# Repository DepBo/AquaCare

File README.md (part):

# AquaCare

AquaCare là hệ thống theo dõi và quản lý nuôi trồng thủy sản, gồm ứng dụng web, ứng dụng di động và backend kết nối dữ liệu cảm biến với thiết bị trong ao/bể.

Trong quá trình nuôi, chất lượng nước và trạng thái thiết bị có thể thay đổi nhanh, trong khi việc kiểm tra thủ công thường tốn thời gian và khó theo dõi liên tục. AquaCare tập trung đưa dữ liệu từ thiết bị IoT về một nơi để người nuôi theo dõi, nhận cảnh báo và chủ động điều khiển một số thiết bị từ xa. Hệ thống đồng thời cung cấp các màn hình quản lý cho khách hàng, nhân viên và quản trị viên.

## Giới thiệu chức năng

### Theo dõi môi trường nuôi

Thiết bị gửi dữ liệu cảm biến về hệ thống thông qua MQTT. Backend tiếp nhận dữ liệu, xử lý và lưu vào Supabase để các ứng dụng truy vấn. Các chỉ số được sử dụng trong luồng theo dõi bao gồm nhiệt độ nước, độ pH, TDS và trạng thái mực nước. Dashboard giúp người dùng quan sát tình trạng hiện tại; phần lịch sử hỗ trợ xem lại biến động theo thời gian.

Ngưỡng đánh giá có thể được cấu hình theo loài nuôi. Dữ liệu được phân loại thành trạng thái bình thường, cần chú ý hoặc nguy hiểm để người vận hành nhận biết nhanh khi môi trường vượt khỏi khoảng phù hợp.

### Cảnh báo và thông báo

Khi chỉ số vượt ngưỡng hoặc phát hiện điều kiện bất thường, backend tạo cảnh báo gắn với bể và thiết bị liên quan. Hệ thống hỗ trợ gửi email và thông báo đẩy Firebase Cloud Messaging khi thông tin dịch vụ đã được cấu hình. Cơ chế xử lý cảnh báo có lọc và gộp trạng thái nhằm hạn chế gửi lặp liên tục cho cùng một tình trạng.

### Điều khiển thiết bị

Người dùng có thể gửi lệnh điều khiển relay từ giao diện. Backend xác định thiết bị theo bể nuôi, phát lệnh qua MQTT và cập nhật trạng thái vào cơ sở dữ liệu. Endpoint lệnh thô cho phép chuyển một chuỗi lệnh tới thiết bị theo giao thức phần cứng đã triển khai. Tác vụ hẹn giờ chạy trong backend hỗ trợ các luồng điều khiển có lịch.

### Tài khoản và phân quyền

Hệ thống có luồng đăng ký, đăng nhập và khôi phục mật khẩu. Khu vực sau đăng nhập được phân theo vai trò: khách hàng sử dụng dashboard nuôi trồng; nhân viên truy cập màn hình nghiệp vụ; quản trị viên quản lý cấu hình và dữ liệu hệ thống. Các trang bảo vệ kiểm tra phiên Supabase và vai trò người dùng trước khi hiển thị.

### Quản lý vận hành và dịch vụ

Giao diện quản trị có các khu vực quản lý loài cá, thiết bị, nhân viên, đơn hàng và gói dịch vụ. Dữ liệu thiết bị có thể được theo dõi theo phiên bản và trạng thái sử dụng/kho. Quản trị viên cũng có thể cấu hình các khoảng ngưỡng nhiệt độ, pH và TDS theo loài, giúp hệ thống đánh giá dữ liệu sát với đối tượng nuôi.

Ứng dụng web còn có các trang giới thiệu sản phẩm và gói đăng ký, giỏ hàng, dashboard khách hàng và các trang nhân viên. Ứng dụng Flutter cung cấp trải nghiệm di động với các màn hình tổng quan, cảnh báo, điều khiển và quản trị.

### Kiến trúc tổng quan

```text
Cảm biến / thiết bị IoT
        │ MQTT telemetry và lệnh điều khiển
        ▼
Backend Node.js + Express ───── Firebase: thông báo đẩy
        │                       Email: cảnh báo
        ▼
     Supabase
        ▲
        ├── AquaCare Web (React + TypeScript)
        └── AquaCare App (Flutter)
```

Backend nhận telemetry và xử lý cảnh báo, đồng thời cung cấp API cho đăng nhập, dashboard quản trị và điều khiển thiết bị. Web và ứng dụng di động đọc dữ liệu nghiệp vụ qua Supabase, sử dụng API backend cho các thao tác tương ứng. Supabase đảm nhiệm lưu trữ và xác thực dữ liệu; MQTT là kênh liên lạc với thiết bị.

## Chức năng chính

- Theo dõi dữ liệu chất lượng nước như pH, nhiệt độ, TDS và mực nước.
- Hiển thị lịch sử dữ liệu, trạng thái thiết bị và cảnh báo theo ngưỡng của từng loài.
- Điều khiển relay và gửi lệnh tới phần cứng qua MQTT.
- Quản lý tài khoản, bể nuôi, thiết bị, nhân viên, sản phẩm và gói dịch vụ.
- Gửi cảnh báo email và thông báo đẩy khi được cấu hình.
- Cung cấp giao diện quản trị trên web và ứng dụng di động.

## AquaCare giải quyết vấn đề gì?

Quản lý ao nuôi đòi hỏi người vận hành theo dõi chất lượng nước thường xuyên, nhận biết sớm các dấu hiệu bất thường và phản ứng kịp thời. Khi số lượng bể tăng lên, việc ghi chép thủ công khiến dữ liệu khó tổng hợp, khó đối chiếu và có thể bỏ lỡ những thay đổi quan trọng giữa các lần kiểm tra.

AquaCare kết hợp thiết bị cảm biến, phần mềm và lưu trữ dữ liệu để hỗ trợ các công việc đó trên cùng một hệ thống. Người dùng có thể xem thông tin từ nhiều bể, tra cứu lại lịch sử, nhận cảnh báo khi chỉ số lệch khỏi ngưỡng, và gửi lệnh đến các thiết bị được kết nối. Ngoài theo dõi kỹ thuật, hệ thống còn có các chức năng quản lý người dùng, nhân viên, thiết bị, đơn hàng và gói dịch vụ.

> AquaCare là công cụ hỗ trợ quan sát và vận hành. Chất lượng kết quả phụ thuộc vào việc hiệu chuẩn cảm biến, kết nối mạng, cấu hình ngưỡng và cấu hình dịch vụ ngoài hệ thống.

## Các nhóm người dùng

### Khách hàng và người nuôi

Khách hàng sử dụng dashboard để xem bể nuôi thuộc tài khoản của mình, theo dõi các chỉ số môi trường và lịch sử, xem cảnh báo, cũng như sử dụng các thao tác điều khiển được cấp quyền. Giao diện web và ứng dụng di động hướng đến việc giúp người nuôi nắm nhanh tình trạng tổng thể rồi mở thông tin chi tiết khi cần.

Khu vực khách hàng trên web còn có các nội dung giới thiệu sản phẩm, gói dịch vụ, giỏ hàng và thông tin liên hệ. Việc truy cập các màn hình được bảo vệ dựa trên phiên xác thực và vai trò tài khoản.

### Nhân viên

Khu vực nhân viên phục vụ các tác vụ vận hành được phân công. Backend dashboard tổng hợp những thông tin như đơn hàng chờ xử lý, công việc đóng gói, đơn đang giao, thiết bị đã được gán và số lượng nhân viên. Màn hình quản trị còn tổ chức vai trò nhân viên theo nhóm công việc như kho, giao hàng, hỗ trợ và bảo trì.

### Quản trị viên

Quản trị viên quản lý cấu hình và dữ liệu vận hành của hệ thống. Các phân hệ hiện diện trong giao diện gồm tổng quan, loài nuôi, thiết bị, nhân viên, đơn hàng và gói cước. Tùy dữ liệu và quyền đã thiết lập, quản trị viên có thể quản lý thông tin loài, ngưỡng môi trường, phân bổ thiết bị, tài khoản nhân viên, trạng thái đơn hàng và đặc tính các gói dịch vụ.

## Mô tả chức năng chi tiết

### 1. Dashboard và quản lý bể nuôi

Dashboard tập trung thông tin theo bể nuôi để người vận hành không phải truy cập nhiều nguồn dữ liệu riêng lẻ. Tùy cấu hình dữ liệu, dashboard hiển thị thông số mới nhất, trạng thái chất lượng nước, cảnh báo và hoạt động điều khiển. Người dùng có thể chọn bể cần xem và đi sâu vào biểu đồ hoặc lịch sử cảm biến.

Các thành phần giao diện hỗ trợ tổng quan bể và phân tích lịch sử. Ứng dụng Flutter có màn hình tổng quan, màn hình chi tiết cảm biến và các tiện ích biểu đồ cảnh báo. Giao diện web có dashboard khách hàng và bảng điều khiển thiết bị.

### 2. Giám sát cảm biến và lịch sử

Backend nhận telemetry theo topic MQTT của thiết bị, đối chiếu thiết bị với bể trong cơ sở dữ liệu, sau đó lưu các giá trị hợp lệ vào bảng lịch sử. Các luồng dữ liệu hiện có đề cập đến pH, nhiệt độ, TDS và tình trạng mực nước. Người dùng có thể xem lại dữ liệu theo thời gian nhằm nhận biết xu hướng thay đổi, thay vì chỉ nhìn vào một số đo tại thời điểm hiện tại.

Lịch sử cũng giúp việc xem xét cảnh báo có thêm bối cảnh: người vận hành có thể đánh giá chỉ số đã thay đổi ra sao, bất thường mới xuất hiện hay đã kéo dài, và cần kiểm tra thiết bị hoặc nguồn nước hay không. Độ chính xác của kết luận phụ thuộc vào cảm biến và tần suất thiết bị gửi dữ liệu.

### 3. Đánh giá ngưỡng theo loài

Mỗi loài thủy sản có điều kiện môi trường phù hợp khác nhau. AquaCare tổ chức cấu hình ngưỡng theo loài để backend và giao diện có thể so sánh dữ liệu cảm biến với khoảng đánh giá tương ứng. Với các chỉ số có ngưỡng tốt và ngưỡng cảnh báo, dữ liệu được phân loại thành `Good`, `Warn` hoặc `Danger`.

Quản trị viên có thể quản lý loài và các khoảng giá trị môi trường được hệ thống sử dụng. Nên xác minh ngưỡng với yêu cầu thực tế của đối tượng nuôi trước khi đưa vào vận hành; cài đặt ứng dụng không thay thế tư vấn chuyên môn hoặc hiệu chuẩn thiết bị.

### 4. Cảnh báo môi trường

Khi chỉ số nằm ngoài khoảng được cấu hình hoặc trạng thái mực nước không bình thường, backend có thể ghi nhận sự kiện vào lịch sử cảnh báo. Cảnh báo được gắn với bể, thiết bị, loại chỉ số, giá trị thực tế và nội dung mô tả để tiện tra cứu.

Luồng cảnh báo có thể kiểm tra cấu hình nhận thông báo của bể, thông tin tài khoản và thời điểm cảnh báo gần nhất. Bộ lọc cooldown/gộp trạng thái giúp hạn chế việc phát đi nhiều thông báo lặp trong một khoảng ngắn. Người vận hành vẫn có thể mở màn hình cảnh báo để xem sự kiện đã lưu.

### 5. Gửi email và thông báo đẩy

Backend hỗ trợ email cảnh báo. Khi cấu hình `BREVO_API_KEY`, email được gửi qua API HTTPS của Brevo; nếu không có khóa này, backend có thể dùng Gmail SMTP với `EMAIL_USER` và `EMAIL_PASS` khi môi trường cho phép. Chi tiết cấu hình triển khai email được ghi trong `AquaCare_Backend/ALERT_EMAIL.md`.

Thông báo đẩy được tích hợp qua Firebase Cloud Messaging. Ứng dụng web có luồng xin quyền trình duyệt và lấy token; ứng dụng Flutter khởi tạo Firebase Messaging và đồng bộ token sau khi đăng nhập. Backend cần thông tin Firebase Admin hợp lệ để gửi thông báo. Người dùng cũng cần cấp quyền thông báo trên trình duyệt hoặc thiết bị.

### 6. Điều khiển relay và lệnh MQTT

Từ bảng điều khiển, người dùng có thể gửi yêu cầu bật/tắt relay. Backend nhận mã bể, chân relay, trạng thái mong muốn và trường trạng thái cần cập nhật. Sau đó backend tra thiết bị theo mã bể, lấy địa chỉ MAC, gửi thông điệp MQTT tới topic lệnh của thiết bị và lưu trạng thái relay vào Supabase.

Endpoint gửi lệnh thô nhận mã bể cùng chuỗi lệnh, sau đó chuyển lệnh đến topic MQTT tương ứng với địa chỉ MAC. Lệnh chính xác cần phù hợp giao thức firmware của thiết bị. Việc gửi lệnh chỉ được xem là thành công hoàn toàn khi thiết bị nhận và thực hiện lệnh; phản hồi HTTP của backend chủ yếu xác nhận quá trình gửi/xử lý ở phía server.

### 7. Lịch điều khiển và mô phỏng phần cứng

Backend có worker xử lý tác vụ hẹn giờ và lịch điều khiển thiết bị. Web có tiện ích xử lý thời gian lịch thiết bị, còn backend có `timer_worker.js` để kiểm tra và phát lệnh theo lịch đã lưu. `hardware_simulator.js` hỗ trợ mô phỏng gửi telemetry trong quá trình phát triển hoặc trình diễn khi chưa có thiết bị thật; cần cấu hình Supabase trước khi chạy.

### 8. Đăng nhập và quản lý phiên

Web có màn hình đăng nhập, đăng ký, quên mật khẩu và đặt lại mật khẩu. Backend cung cấp API đăng ký/đăng nhập, trong khi Supabase được dùng cho xác thực và dữ liệu hồ sơ. Các trang dashboard, nhân viên và quản trị viên kiểm tra vai trò trước khi cho truy cập. Nếu phiên không hợp lệ hoặc vai trò không khớp với khu vực được yêu cầu, ứng dụng chuyển người dùng về trang phù hợp.

Ứng dụng di động có màn hình khởi động, hướng dẫn ban đầu, đăng nhập và đăng ký. Ứng dụng có thể ghi nhớ lựa chọn đăng nhập, khôi phục phiên khi khởi chạy và điều hướng theo vai trò đã xác thực.

### 9. Quản trị thiết bị

Phân hệ thiết bị tập trung thông tin gắn với bể, địa chỉ MAC, phiên bản phần cứng và trạng thái sử dụng. Màn hình quản trị cung cấp bộ lọc theo phiên bản thiết bị (V1–V4) và trạng thái như đang dùng, đã được mua hoặc còn trong kho. Việc gán đúng thiết bị với đúng bể là điều kiện để backend định tuyến lệnh MQTT và gắn telemetry với dữ liệu nuôi.

### 10. Quản lý loài và điều kiện nuôi

Danh mục loài giúp hệ thống lưu thông tin đối tượng nuôi và các ngưỡng môi trường áp dụng. Dữ liệu này được dùng ở cả khâu đánh giá cảm biến lẫn giao diện hiển thị trạng thái. Khi tạo hoặc cập nhật ngưỡng, cần đảm bảo giá trị nhỏ nhất không lớn hơn giá trị lớn nhất và các khoảng tốt/cảnh báo được thiết lập nhất quán.

### 11. Quản lý nhân viên và công việc

Quản trị viên có thể tổ chức nhân viên theo vai trò nghiệp vụ. Dashboard backend hiện tổng hợp một số chỉ số vận hành, bao gồm số nhân viên, đơn hàng chờ xử lý, công việc đóng gói đang thực hiện và đơn đang giao. Những dữ liệu này giúp theo dõi công việc nội bộ song song với tình trạng kỹ thuật của thiết bị.

### 12. Sản phẩm, đơn hàng và gói dịch vụ

Web có trang sản phẩm, gói đăng ký và giỏ hàng. Schema cơ sở dữ liệu có các bảng liên quan đến sản phẩm, đơn hàng, chi tiết đơn, mục giỏ hàng, gói đăng ký và đăng ký gói của người dùng. Phần quản trị đơn hàng hỗ trợ theo dõi các trạng thái như chờ duyệt, đã duyệt, đang giao và đã giao.

### 13. Giao diện web và ứng dụng di động

Web được xây dựng bằng React, TypeScript và Vite. Ứng dụng Flutter chứa các màn hình khách hàng, cảnh báo, điều khiển, nhân viên và quản trị, sử dụng chung Supabase làm nguồn dữ liệu nghiệp vụ. Tùy vai trò và nền tảng, một số tính năng hoặc cấu hình thông báo có thể khác nhau.

### 14. Cấu hình giao diện khách hàng

Ứng dụng di động lưu tùy chọn giao diện khách hàng và hỗ trợ tùy chỉnh chế độ sáng/tối. Giao diện dashboard và các biểu đồ giúp trình bày thông tin môi trường theo dạng trực quan hơn để người vận hành dễ nhận biết điểm cần chú ý.

## Cấu trúc dự án

```text
AquaCare/
├── AquaCare_Backend/   # API Express, MQTT, xử lý cảnh báo và tác vụ hẹn giờ
├── AquaCare_Web/       # Giao diện React + TypeScript, chạy bằng Vite
├── AquaCare_App/       # Ứng dụng Flutter cho Android, iOS, Windows và các nền tảng Flutter hỗ trợ
├── migrations/         # Các tệp migration cơ sở dữ liệu
├── schema.sql          # Schema cơ sở dữ liệu
├── database.txt        # Tài liệu/thông tin cơ sở dữ liệu
└── README.md
```

## Yêu cầu

- Node.js và npm.
- Flutter SDK tương thích với phiên bản Dart trong `AquaCare_App/pubspec.yaml`.
- Tài khoản/dự án Supabase đã được thiết lập schema.
- Tài khoản Firebase nếu cần gửi thông báo đẩy; thông tin broker MQTT nếu cần kết nối phần cứng.

## Chạy backend

```bash
cd AquaCare_Backend
npm install
node server.js
```

Backend mặc định chạy tại `http://localhost:5000`. Kiểm tra trạng thái bằng `GET /api/health`.

Tạo `AquaCare_Backend/.env` với các giá trị phù hợp:

```dotenv
PORT=5000
SUPABASE_URL=https://<project-ref>.supabase.co
SUPABASE_SERVICE_ROLE_KEY=<supabase-service-role-key>

# Email cảnh báo: dùng SMTP Gmail khi chạy local
EMAIL_USER=<email>
EMAIL_PASS=<app-password>

# Tùy chọn trên môi trường triển khai: gửi email qua Brevo HTTPS
BREVO_API_KEY=<brevo-api-key>
ALERT_EMAIL_FROM=<verified-sender-email>

# Firebase Admin: JSON service account được tuần tự hóa thành một dòng
FIREBASE_SERVICE_ACCOUNT=<service-account-json>
```

Nếu không đặt `FIREBASE_SERVICE_ACCOUNT`, backend tìm tệp `config/firebase-service-account.json`. Không commit tệp khóa hoặc biến môi trường chứa bí mật. Thông tin kết nối HiveMQ hiện được khai báo trong `AquaCare_Backend/server.js`; chuyển các thông tin đó sang biến môi trường trước khi sử dụng cấu hình broker riêng hoặc công khai mã nguồn.

## Chạy ứng dụng web

```bash
cd AquaCare_Web
npm install
npm run dev
```

Vite in địa chỉ truy cập local ra terminal (thông thường là `http://localhost:5173`). Các lệnh có sẵn:

```bash
npm run build
npm run preview
```

Có thể tạo `AquaCare_Web/.env.local` để cấu hình dịch vụ:

```dotenv
VITE_API_URL=http://localhost:5000
VITE_SUPABASE_URL=https://<project-ref>.supabase.co
VITE_SUPABASE_ANON_KEY=<supabase-anon-key>
```

Web có URL mặc định cho backend triển khai. Khi phát triển local, cần đặt `VITE_API_URL` để các API đăng nhập, điều khiển thiết bị và dashboard trỏ tới backend local. Các biến `VITE_*` được đưa vào mã phía trình duyệt; chỉ dùng khóa Supabase anon/public key, tuyệt đối không đưa service role key vào web.

## Chạy ứng dụng Flutter

Tạo `AquaCare_App/.env`:

```dotenv
SUPABASE_URL=https://<project-ref>.supabase.co
SUPABASE_ANON_KEY=<supabase-anon-key>
```

Sau đó chạy:

```bash
cd AquaCare_App
flutter pub get
flutter run
```

Ứng dụng cũng hỗ trợ URL backend dashboard qua Dart define:

```bash
flutter run --dart-define=ADMIN_DASHBOARD_API_URL=http://localhost:5000
```

## API chính

| Phương thức | Đường dẫn | Mô tả |
|---|---|---|
| `GET` | `/api/health` | Kiểm tra backend hoạt động |
| `POST` | `/api/auth/register` | Đăng ký tài khoản |
| `POST` | `/api/auth/login` | Đăng nhập |
| `GET` | `/api/admin/dashboard` | Dữ liệu dashboard quản trị |
| `POST` | `/api/device/relay` | Điều khiển relay qua MQTT |
| `POST` | `/api/device/command` | Gửi lệnh thô tới thiết bị qua MQTT |

Các API quản trị yêu cầu phiên đăng nhập và quyền admin. Payload chi tiết xem trong mã nguồn tại `AquaCare_Backend/routes/` và phần xử lý endpoint thiết bị trong `AquaCare_Backend/server.js`.

## Cơ sở dữ liệu và kiểm tra

- Dùng `schema.sql` để tham khảo schema ban đầu; các cập nhật sau có thể nằm trong `migrations/`.
- Backend có các bài kiểm tra Node.js trong `AquaCare_Backend/test/`.
- Web có kiểm tra trong `AquaCare_Web/tests/`.
- Ứng dụng Flutter dùng cấu hình và lệnh chuẩn của Flutter; xem `AquaCare_App/README.md`.

## Bảo mật

- Không commit `.env`, khóa Supabase service role, Firebase service account hoặc mật khẩu email.
- Chỉ dùng Supabase anon key trong ứng dụng web/di động và cấu hình Row Level Security phù hợp trong Supabase.
- Các credential MQTT đang có trong mã nguồn backend cần được thay/thu hồi nếu repository từng được chia sẻ công khai.
- Giới hạn CORS và cấu hình endpoint theo các domain triển khai thực tế trước khi đưa hệ thống lên production.

## AquaCare giải quyết vấn đề gì?

Quản lý ao nuôi đòi hỏi người vận hành theo dõi chất lượng nước thường xuyên, nhận biết sớm dấu hiệu bất thường và phản ứng kịp thời. Khi số lượng bể tăng, ghi chép thủ công khiến dữ liệu khó tổng hợp và có thể bỏ lỡ thay đổi giữa các lần kiểm tra. AquaCare kết hợp thiết bị cảm biến, phần mềm và lưu trữ dữ liệu để người dùng xem tình trạng nhiều bể, tra cứu lịch sử, nhận cảnh báo và điều khiển thiết bị từ xa. Hệ thống cũng có các chức năng quản lý nhân viên, thiết bị, đơn hàng và gói dịch vụ.

> AquaCare là công cụ hỗ trợ quan sát và vận hành. Kết quả phụ thuộc vào độ chính xác cảm biến, kết nối mạng, ngưỡng cấu hình và dịch vụ ngoài hệ thống.

## Nhóm người dùng

### Khách hàng và người nuôi

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
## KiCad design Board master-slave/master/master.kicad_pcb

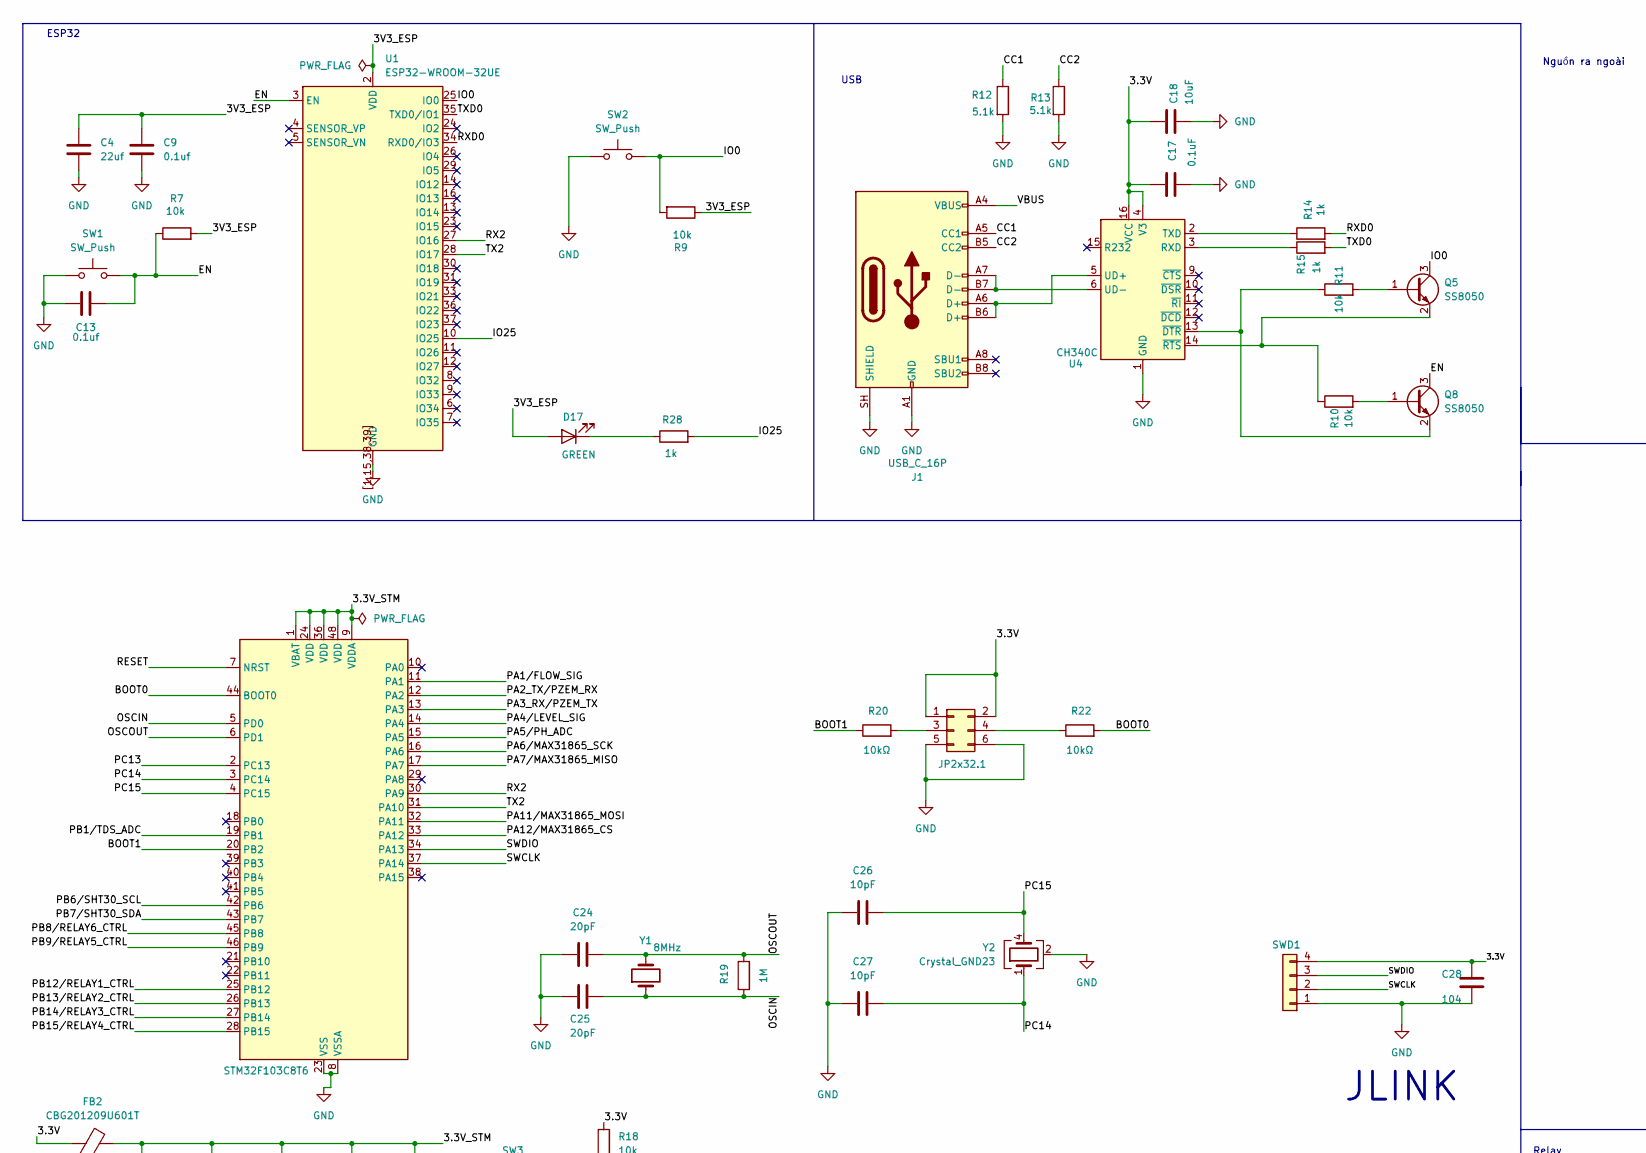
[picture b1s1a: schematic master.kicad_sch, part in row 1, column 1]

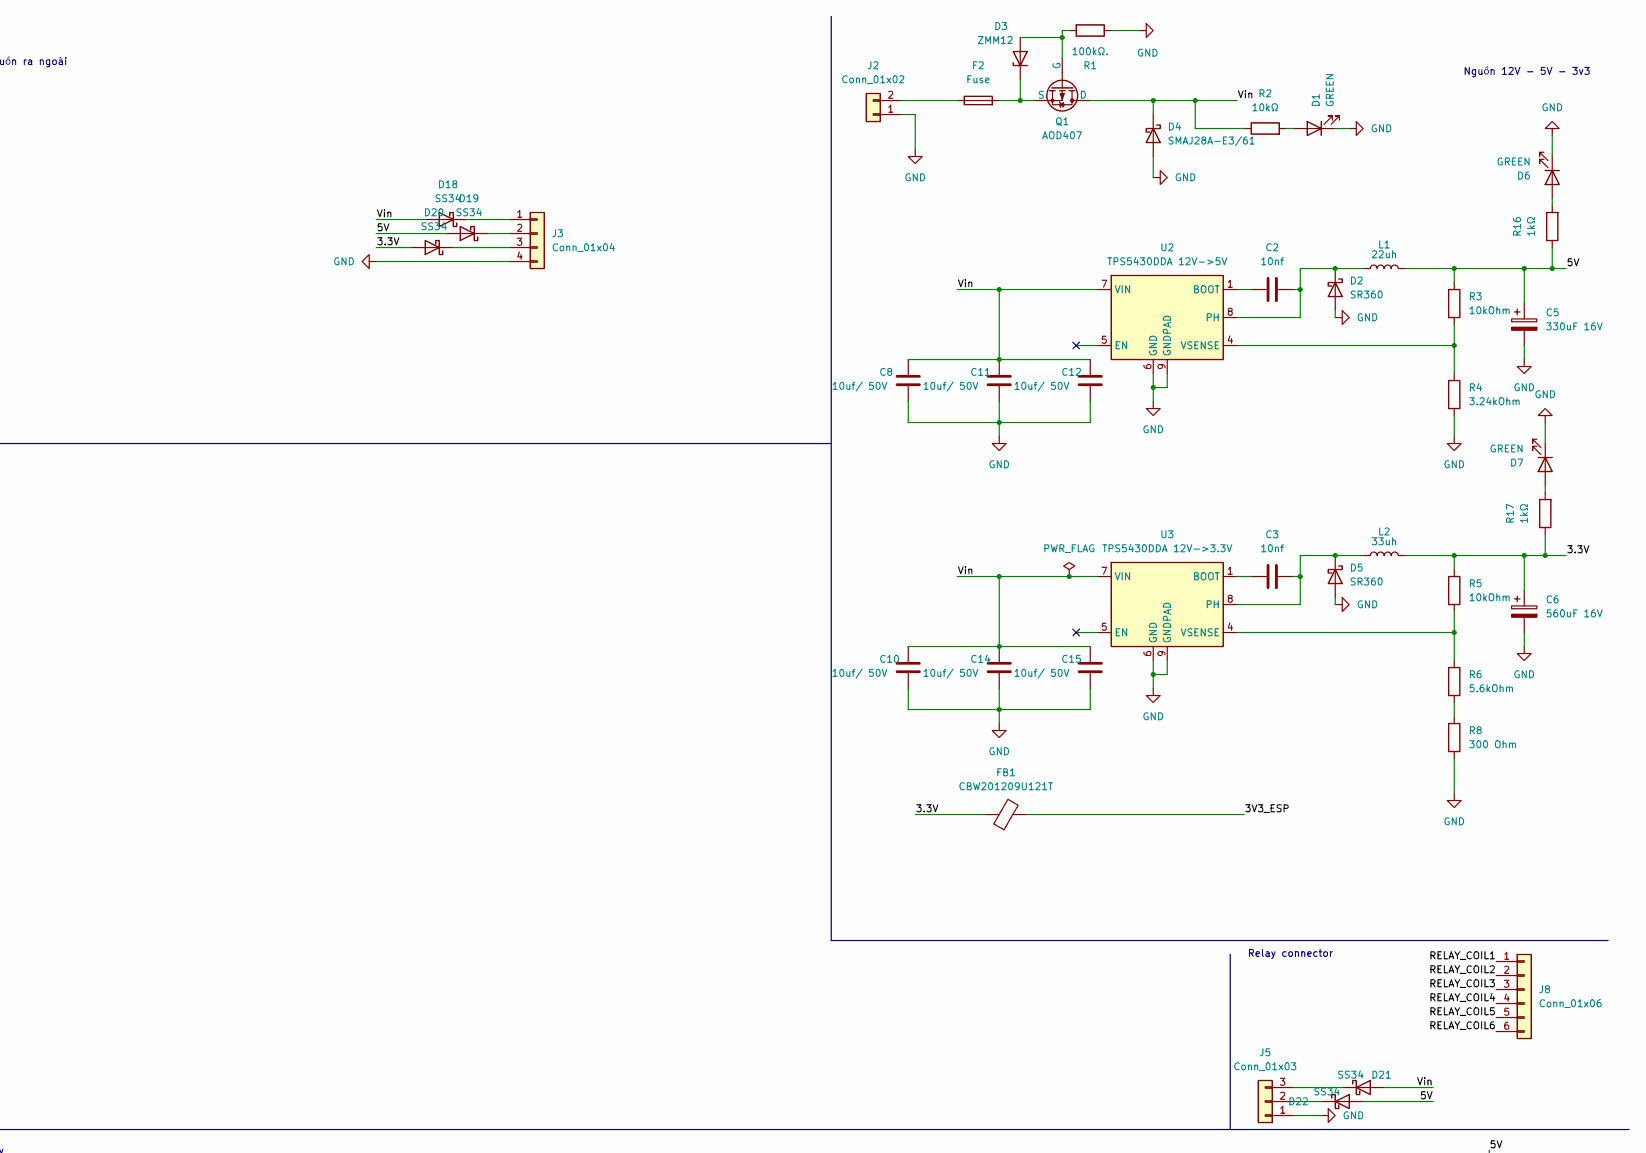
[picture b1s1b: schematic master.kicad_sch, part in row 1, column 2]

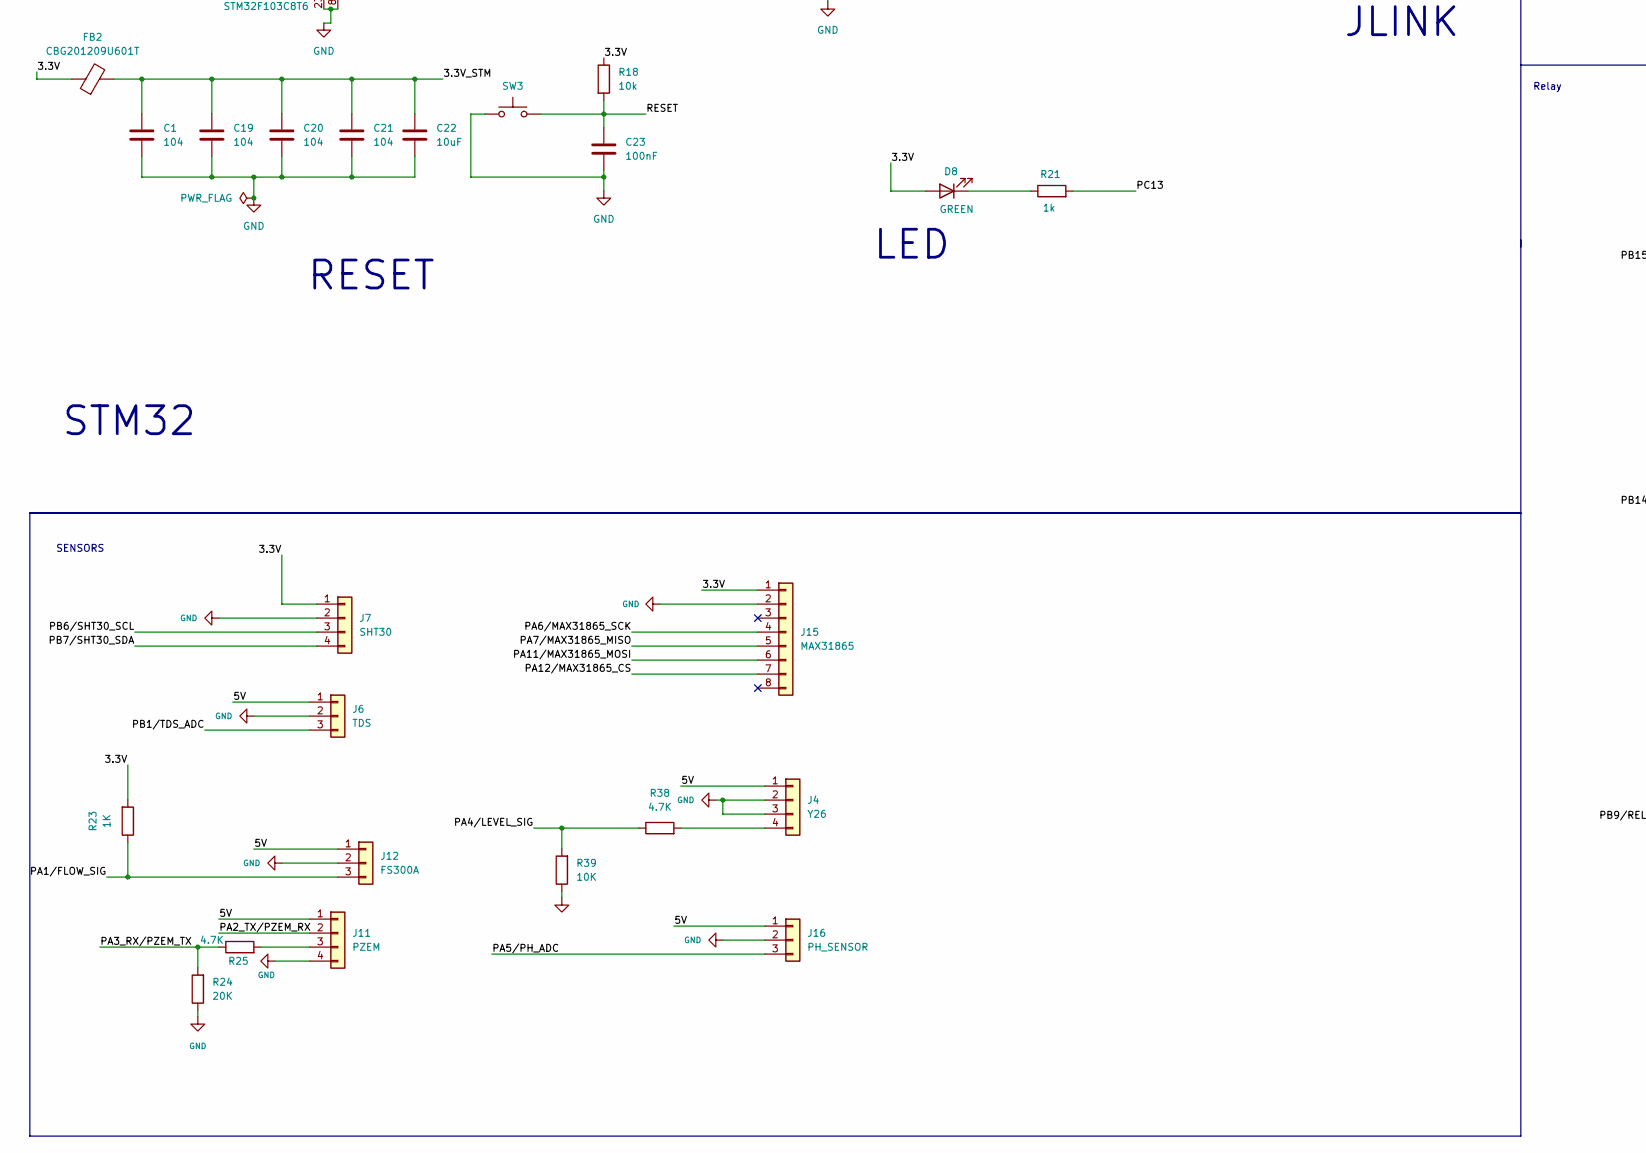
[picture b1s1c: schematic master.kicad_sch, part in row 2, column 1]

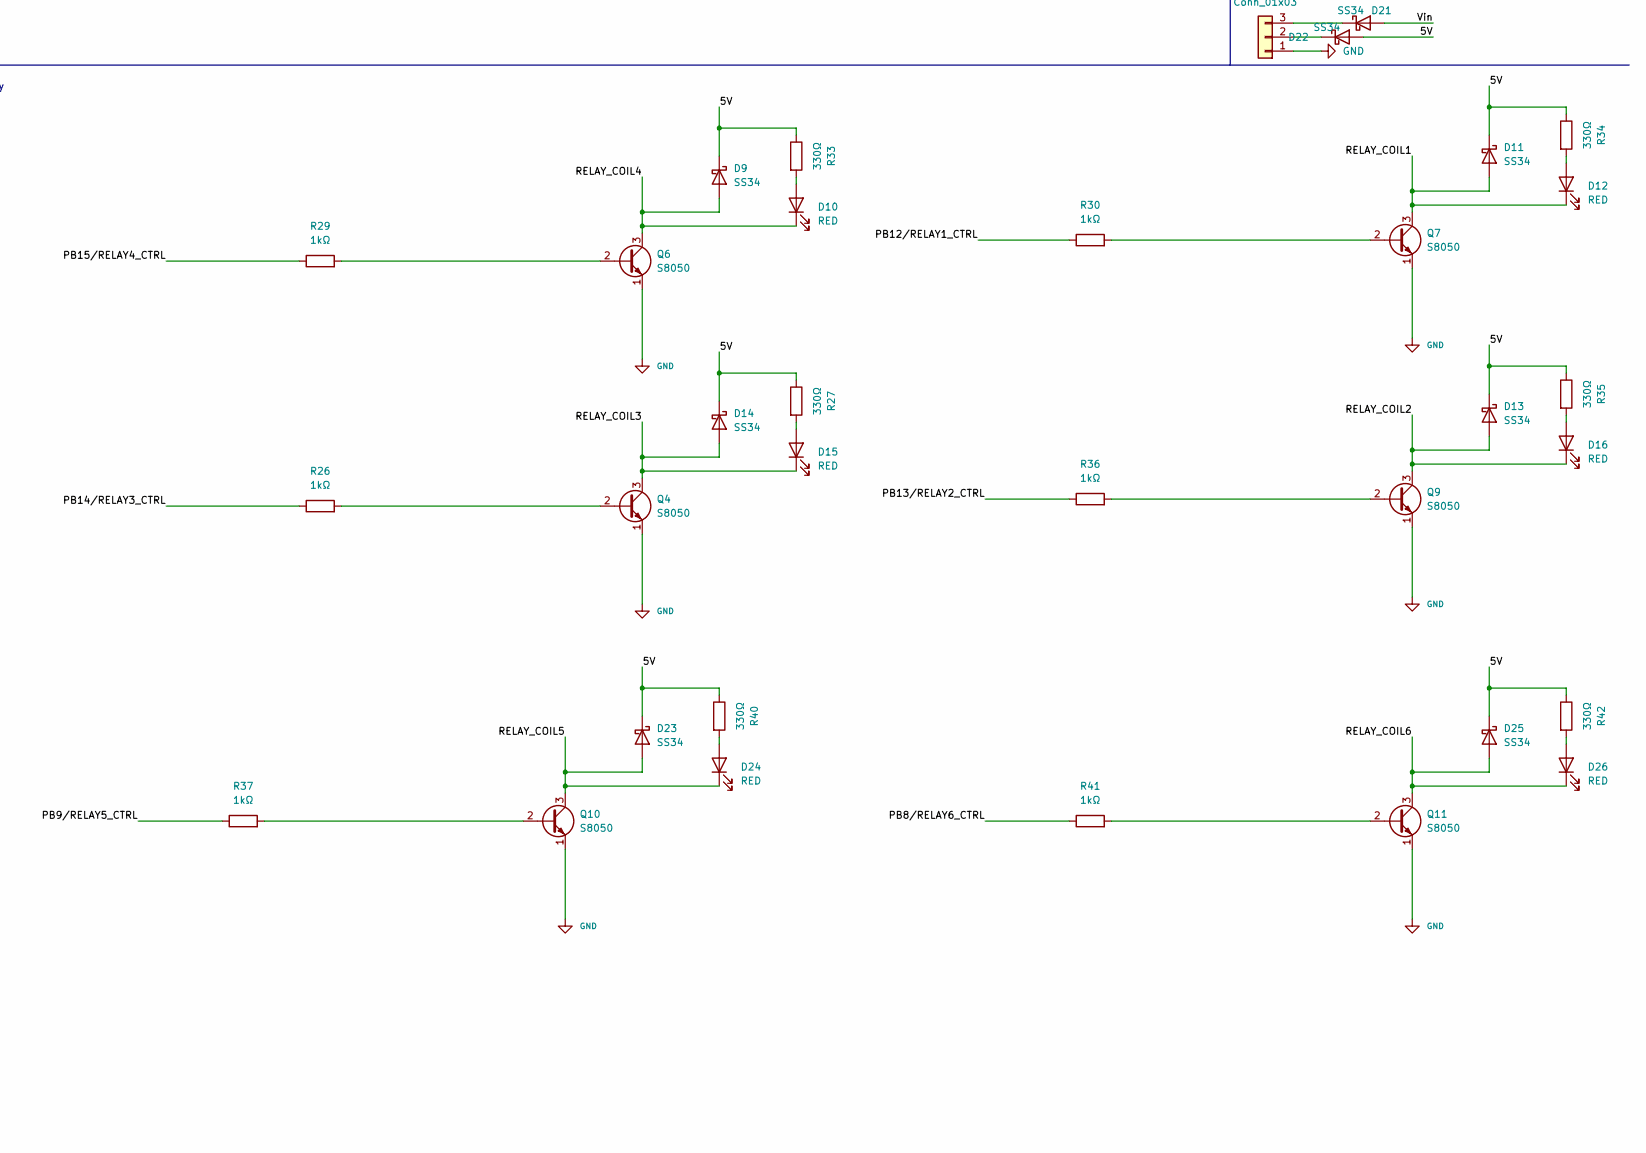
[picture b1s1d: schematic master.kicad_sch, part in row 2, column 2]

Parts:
C1, C19, C20, C21: 104; C_0805_2012Metric
C2, C3: 10nf; C_0805_2012Metric_Pad1.18x1.45mm_HandSolder
C4: 22uf; C_0805_2012Metric_Pad1.18x1.45mm_HandSolder
C5: 330uF 16V; CP_Radial_D6.3mm_P2.50mm
C6: 560uF 16V; CP_Radial_D6.3mm_P2.50mm
C8, C10, C11, C12, C14, C15: 10uf/ 50V; C_0805_2012Metric_Pad1.18x1.45mm_HandSolder
C9: 0.1uf; C_0805_2012Metric_Pad1.18x1.45mm_HandSolder
C13: 0.1uf; C_Disc_D5.0mm_W2.5mm_P2.50mm
C17: 0.1uF; C_0603_1608Metric
C18: 10uF; C_0603_1608Metric
C22: 10uF; C_0805_2012Metric
C23: 100nF; C_Disc_D5.0mm_W2.5mm_P2.50mm
C24, C25: 20pF; C_0603_1608Metric_Pad1.08x0.95mm_HandSolder
C26, C27: 10pF; C_0805_2012Metric
C28: 104; C_Disc_D5.0mm_W2.5mm_P2.50mm
D1, D6, D7, D8, D17: GREEN; LED_0805_2012Metric
D2, D5: SR360; D_DO-201AD_P15.24mm_Horizontal
D3: ZMM12; D_MiniMELF
D4: SMAJ28A-E3/61; D_SMA
D9, D11, D13, D14, D18, D19, D20, D21, D22, D23, D25: SS34; D_SMA
D10, D12, D15, D16, D24, D26: RED; LED_0805_2012Metric
F2: Fuse; Fuse_1812_4532Metric
FB1: CBW201209U121T; L_0805_2012Metric_Pad1.05x1.20mm_HandSolder
FB2: CBG201209U601T; L_0805_2012Metric_Pad1.05x1.20mm_HandSolder
J1: USB_C_16P; USB_C_Receptacle_GCT_USB4105-xx-A_16P_TopMnt_Horizontal
J2: Conn_01x02; TerminalBlock_Phoenix_PT-1,5-2-5.0-H_1x02_P5.00mm_Horizontal
J3: Conn_01x04; TerminalBlock_Phoenix_PT-1,5-4-5.0-H_1x04_P5.00mm_Horizontal
J4: Y26; JST_XH_B4B-XH-AM_1x04_P2.50mm_Vertical
J5: Conn_01x03; TerminalBlock_Phoenix_PT-1,5-3-5.0-H_1x03_P5.00mm_Horizontal
J6: TDS; JST_XH_B3B-XH-AM_1x03_P2.50mm_Vertical
J7: SHT30; JST_XH_B4B-XH-AM_1x04_P2.50mm_Vertical
J8: Conn_01x06; TerminalBlock_Phoenix_PT-1,5-6-5.0-H_1x06_P5.00mm_Horizontal
J11: PZEM; JST_XH_B4B-XH-AM_1x04_P2.50mm_Vertical
J12: FS300A; JST_XH_B3B-XH-AM_1x03_P2.50mm_Vertical
J15: MAX31865; JST_XH_B8B-XH-AM_1x08_P2.50mm_Vertical
J16: PH_SENSOR; JST_XH_B3B-XH-AM_1x03_P2.50mm_Vertical
JP2x32.1: Conn_02x03_Odd_Even; PinHeader_2x03_P2.54mm_Vertical
L1: 22uh; L_12x12mm_H8mm
L2: 33uh; L_12x12mm_H8mm
Q1: AOD407; TO-252-2
Q4, Q6, Q7, Q9, Q10, Q11: S8050; TO-92_Inline
Q5, Q8: SS8050; SOT-23
R1: 100kΩ.; R_Axial_DIN0207_L6.3mm_D2.5mm_P7.62mm_Horizontal
R2: 10kΩ; R_Axial_DIN0207_L6.3mm_D2.5mm_P7.62mm_Horizontal
R3, R5: 10kOhm; R_0805_2012Metric
R4: 3.24kOhm; R_0805_2012Metric
R6: 5.6kOhm; R_0805_2012Metric
R7, R9, R18: 10k; R_Axial_DIN0207_L6.3mm_D2.5mm_P7.62mm_Horizontal
R8: 300 Ohm; R_0805_2012Metric
R10, R11: 10k; R_0603_1608Metric
R12, R13: 5.1k; R_0603_1608Metric
R14, R15: 1k; R_0603_1608Metric
R16, R17, R26, R29, R30, R36, R37, R41: 1kΩ; R_Axial_DIN0207_L6.3mm_D2.5mm_P7.62mm_Horizontal
R19: 1M; R_0805_2012Metric
R20, R22: 10kΩ; R_0805_2012Metric
R21, R28: 1k; R_0805_2012Metric
R23: 1K; R_Axial_DIN0207_L6.3mm_D2.5mm_P7.62mm_Horizontal
R24: 20K; R_Axial_DIN0207_L6.3mm_D2.5mm_P7.62mm_Horizontal
R25, R38: 4.7K; R_Axial_DIN0207_L6.3mm_D2.5mm_P7.62mm_Horizontal
R27, R33, R34, R35, R40, R42: 330Ω; R_0805_2012Metric
R39: 10K; R_Axial_DIN0207_L6.3mm_D2.5mm_P7.62mm_Horizontal
SW1, SW2: SW_Push; SW_PUSH_6mm_H5mm
SW3: SW_PUSH_6mm_H5mm
SWD1: Conn_01x04; PinHeader_1x04_P2.54mm_Vertical
U1: ESP32-WROOM-32UE
U2: TPS5430DDA 12V->5V; TI_SO-PowerPAD-8_ThermalVias
U3: TPS5430DDA 12V->3.3V; TI_SO-PowerPAD-8_ThermalVias
U4: CH340C; SOP-16_4.4x10.4mm_P1.27mm
U5: STM32F103C8T6; LQFP-48_7x7mm_P0.5mm
Y1: 8MHz; Crystal_SMD_5032-2Pin_5.0x3.2mm
Y2: Crystal_GND23; Crystal_SMD_Abracon_ABS25-4Pin_8.0x3.8mm

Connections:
/3.3V: C6.1, C17.1, C18.1, C28.2, D8.2 (A), D20.2 (A), FB1.1, FB2.1, J7.1, J15.1, JP2x32.1.1, JP2x32.1.2, L2.2, R5.1, R17.1, R18.1, R23.2, SWD1.4, U4.4 (V3), U4.16 (VCC)
/3.3V_STM: C1.1, C19.1, C20.1, C21.1, C22.1, FB2.2, U5.1 (VBAT), U5.9 (VDDA), U5.24 (VDD), U5.36 (VDD), U5.48 (VDD)
/3V3_ESP: C4.1, C9.1, D17.2 (A), FB1.2, R7.2, R9.1, U1.2 (VDD)
/5V: C5.1, D9.1 (K), D11.1 (K), D13.1 (K), D14.1 (K), D19.2 (A), D22.2 (A), D23.1 (K), D25.1 (K), J4.1, J6.1, J11.1, J12.1, J16.1, L1.2, R3.1, R16.1, R27.1, R33.1, R34.1, R35.1, R40.1, R42.1
/BOOT0: R22.2, U5.44 (BOOT0)
/BOOT1: R20.1, U5.20 (PB2)
/CC1: J1.A5 (CC1), R12.1
/CC2: J1.B5 (CC2), R13.1
/EN: C13.2, Q8.3 (C), R7.1, SW1.2, U1.3 (EN)
/IO0: Q5.3 (C), R9.2, SW2.2, U1.25 (IO0)
/IO25: R28.2, U1.10 (IO25)
/OSCIN: C25.2, R19.1, U5.5 (PD0), Y1.1
/OSCOUT: C24.2, R19.2, U5.6 (PD1), Y1.2
/PA1/FLOW_SIG: J12.3, R23.1, U5.11 (PA1)
/PA2_TX/PZEM_RX: J11.2, U5.12 (PA2)
/PA3_RX/PZEM_TX: R24.2, R25.1, U5.13 (PA3)
/PA4/LEVEL_SIG: R38.1, R39.2, U5.14 (PA4)
/PA5/PH_ADC: J16.3, U5.15 (PA5)
/PA6/MAX31865_SCK: J15.4, U5.16 (PA6)
/PA7/MAX31865_MISO: J15.5, U5.17 (PA7)
/PA11/MAX31865_MOSI: J15.6, U5.32 (PA11)
/PA12/MAX31865_CS: J15.7, U5.33 (PA12)
/PB1/TDS_ADC: J6.3, U5.19 (PB1)
/PB6/SHT30_SCL: J7.3, U5.42 (PB6)
/PB7/SHT30_SDA: J7.4, U5.43 (PB7)
/PB8/RELAY6_CTRL: R41.1, U5.45 (PB8)
/PB9/RELAY5_CTRL: R37.1, U5.46 (PB9)
/PB12/RELAY1_CTRL: R30.1, U5.25 (PB12)
/PB13/RELAY2_CTRL: R36.1, U5.26 (PB13)
/PB14/RELAY3_CTRL: R26.1, U5.27 (PB14)
/PB15/RELAY4_CTRL: R29.1, U5.28 (PB15)
/PC13: R21.2, U5.2 (PC13)
/PC14: C27.2, U5.3 (PC14), Y2.1
/PC15: C26.2, U5.4 (PC15), Y2.4
/RELAY_COIL1: D11.2 (A), D12.1 (K), J8.1, Q7.3 (C)
/RELAY_COIL2: D13.2 (A), D16.1 (K), J8.2, Q9.3 (C)
/RELAY_COIL3: D14.2 (A), D15.1 (K), J8.3, Q4.3 (C)
/RELAY_COIL4: D9.2 (A), D10.1 (K), J8.4, Q6.3 (C)
/RELAY_COIL5: D23.2 (A), D24.1 (K), J8.5, Q10.3 (C)
/RELAY_COIL6: D25.2 (A), D26.1 (K), J8.6, Q11.3 (C)
/RESET: C23.1, R18.2, SW3.2, U5.7 (NRST)
/RX2: U1.27 (IO16), U5.30 (PA9)
/RXD0: R14.2, U1.34 (RXD0/IO3)
/SWCLK: SWD1.2, U5.37 (PA14)
/SWDIO: SWD1.3, U5.34 (PA13)
/TX2: U1.28 (IO17), U5.31 (PA10)
/TXD0: R15.2, U1.35 (TXD0/IO1)
/VBUS: J1.A4 (VBUS), J1.A9 (VBUS), J1.B4 (VBUS), J1.B9 (VBUS)
/Vin: C8.1, C10.1, C11.1, C12.1, C14.1, C15.1, D4.1 (K), D18.2 (A), D21.2 (A), Q1.1 (D), R2.1, U2.7 (VIN), U3.7 (VIN)
GND: C1.2, C4.2, C5.2, C6.2, C8.2, C9.2, C10.2, C11.2, C12.2, C13.1, C14.2, C15.2, C17.2, C18.2, C19.2, C20.2, C21.2, C22.2, C23.2, C24.1, C25.1, C26.1, C27.1, C28.1, D1.1 (K), D2.2 (A), D4.2 (A), D5.2 (A), D6.1 (K), D7.1 (K), J1.A1 (GND), J1.A12 (GND), J1.B1 (GND), J1.B12 (GND), J1.SH (SHIELD), J2.1, J3.4, J4.2, J4.3, J5.1, J6.2, J7.2, J11.4, J12.2, J15.2, J16.2, JP2x32.1.5, JP2x32.1.6, Q4.1 (E), Q6.1 (E), Q7.1 (E), Q9.1 (E), Q10.1 (E), Q11.1 (E), R1.1, R4.2, R8.2, R12.2, R13.2, R24.1, R39.1, SW1.1, SW2.1, SW3.1, SWD1.1, U1.1 (GND), U1.15 (GND), U1.38 (GND), U1.39 (GND), U1.[1,15,38,39] (GND), U2.6 (GND), U2.9 (GNDPAD), U3.6 (GND), U3.9 (GNDPAD), U4.1 (GND), U5.8 (VSSA), U5.23 (VSS), U5.35 (VSS), U5.47 (VSS), Y2.2 (G), Y2.3 (G)
unnamed: D1.2 (A), R2.2
unnamed: C2.2, D2.1 (K), L1.1, U2.8 (PH)
unnamed: D3.2 (A), Q1.2 (G), R1.2
unnamed: D3.1 (K), F2.2, Q1.3 (S)
unnamed: C3.2, D5.1 (K), L2.1, U3.8 (PH)
unnamed: D6.2 (A), R16.2
unnamed: D7.2 (A), R17.2
unnamed: D8.1 (K), R21.1
unnamed: D10.2 (A), R33.2
unnamed: D12.2 (A), R34.2
unnamed: D15.2 (A), R27.2
unnamed: D16.2 (A), R35.2
unnamed: D17.1 (K), R28.1
unnamed: D18.1 (K), J3.1
unnamed: D19.1 (K), J3.2
unnamed: D20.1 (K), J3.3
unnamed: D21.1 (K), J5.3
unnamed: D22.1 (K), J5.2
unnamed: D24.2 (A), R40.2
unnamed: D26.2 (A), R42.2
unnamed: F2.1, J2.2
unnamed: J4.4, R38.2
unnamed: J11.3, R25.2
unnamed: JP2x32.1.3, R20.2
unnamed: JP2x32.1.4, R22.1
unnamed: Q4.2 (B), R26.2
unnamed: Q5.1 (B), R11.2
unnamed: Q5.2 (E), R10.1, U4.14 (~RTS)
unnamed: Q6.2 (B), R29.2
unnamed: Q7.2 (B), R30.2
unnamed: Q8.1 (B), R10.2
unnamed: Q8.2 (E), R11.1, U4.13 (~DTR)
unnamed: Q9.2 (B), R36.2
unnamed: Q10.2 (B), R37.2
unnamed: Q11.2 (B), R41.2
unnamed: R6.2, R8.1
unnamed: C2.1, U2.1 (BOOT)
unnamed: R3.2, R4.1, U2.4 (VSENSE)
unnamed: C3.1, U3.1 (BOOT)
unnamed: R5.2, R6.1, U3.4 (VSENSE)
unnamed: R15.1, U4.3 (RXD)
unnamed: R14.1, U4.2 (TXD)
unnamed: J1.A6 (D+), J1.B6 (D+), U4.5 (UD+)
unnamed: J1.A7 (D-), J1.B7 (D-), U4.6 (UD-)

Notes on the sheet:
Nguồn ra ngoài
RESET
LED
Relay
JLINK
Relay connector
Nguồn 12V - 5V - 3v3
USB
ESP32
STM32
SENSORS

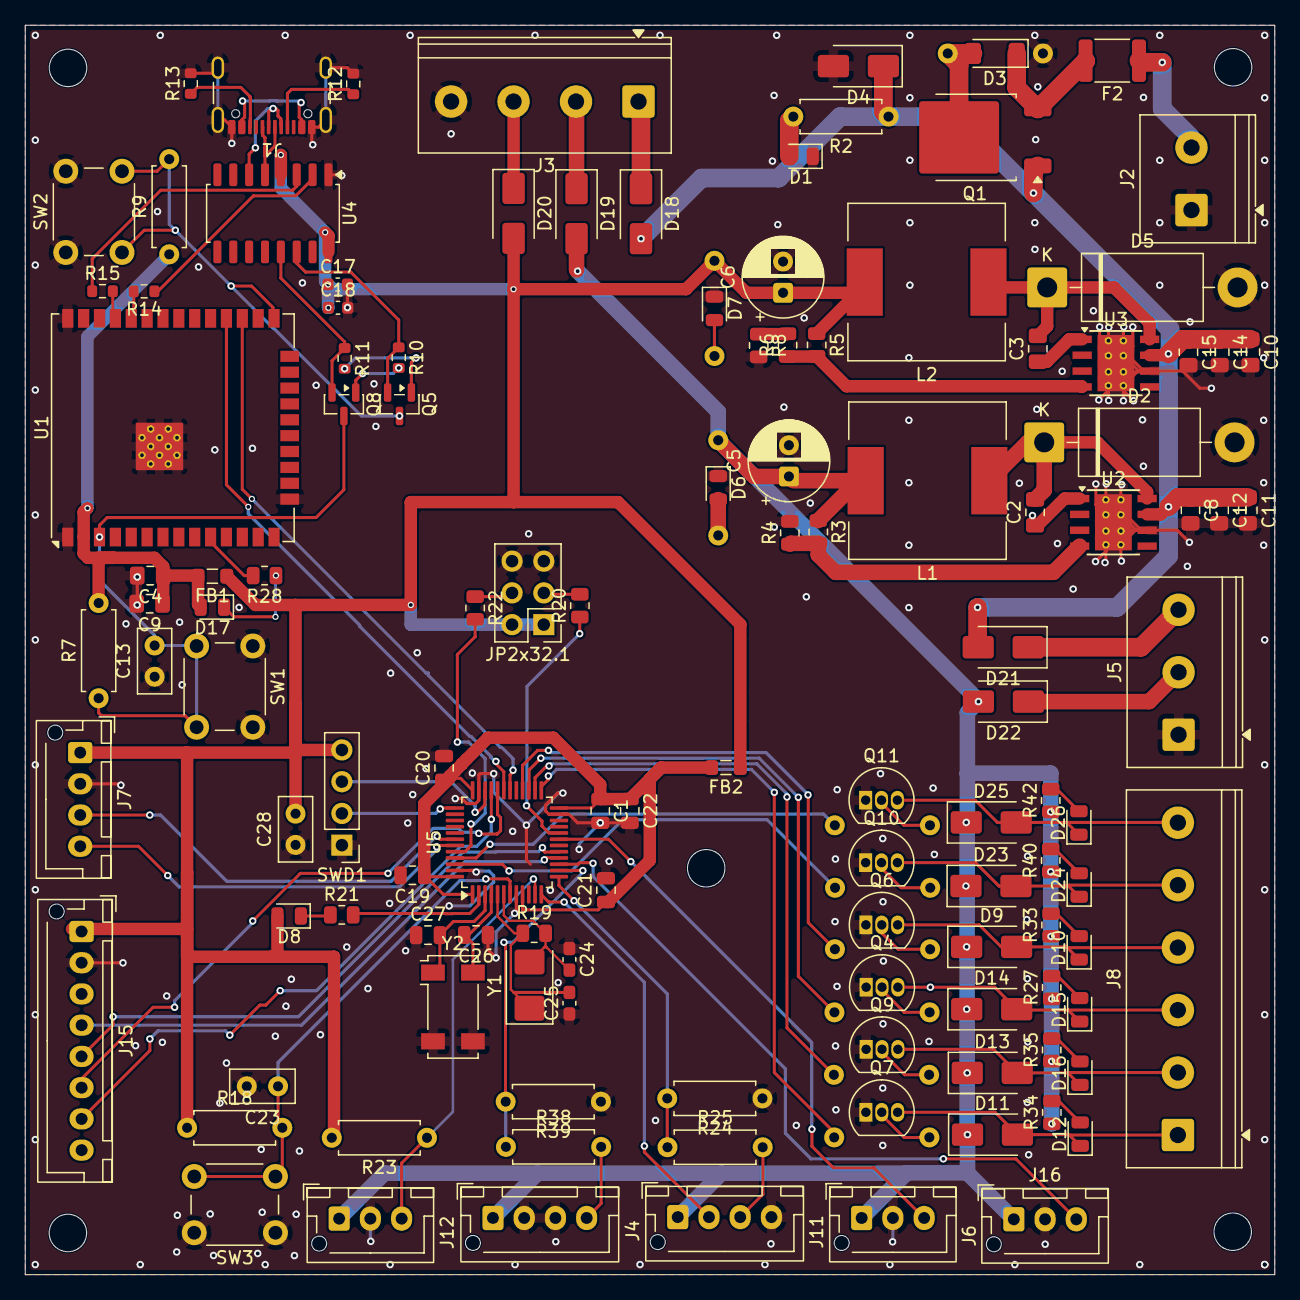
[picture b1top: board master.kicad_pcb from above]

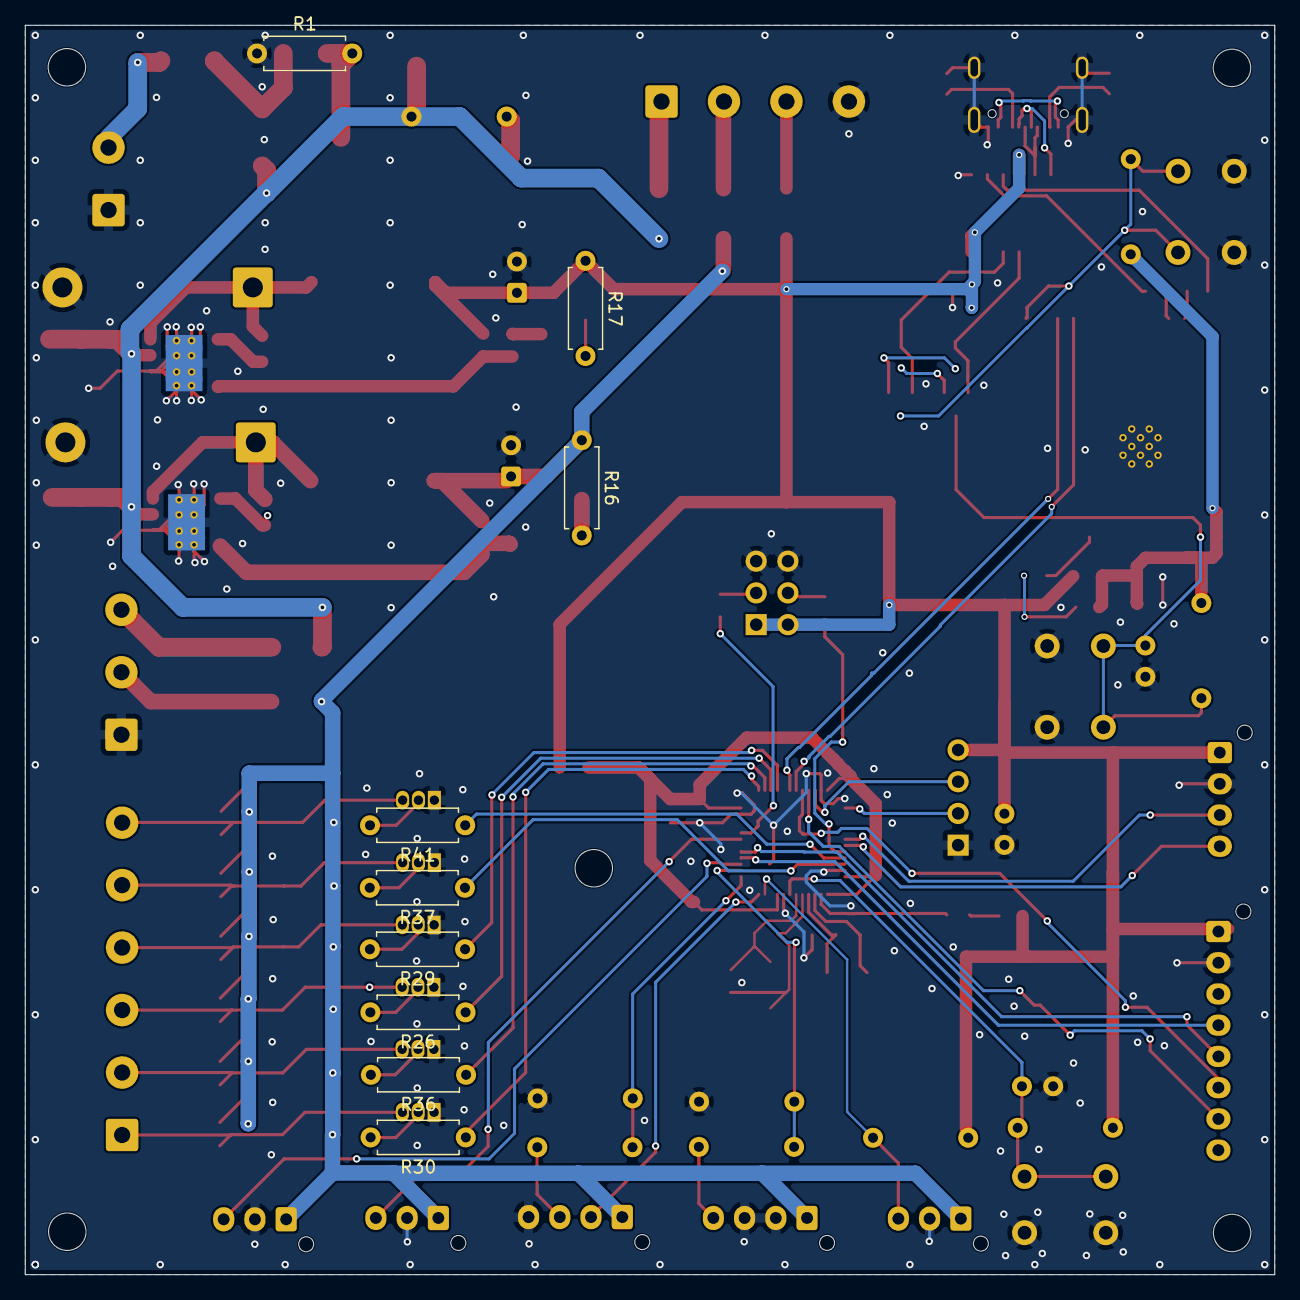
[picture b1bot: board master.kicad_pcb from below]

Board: 2 copper layers, 100.0 x 100.0 mm, 130 parts (9 on the bottom side), 94 nets.

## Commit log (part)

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2026-06-19 Initial project - Aquacare
2026-06-22 Create CNAME
2026-06-22 Tạo app, CRUD hồ cá
2026-06-22 test
2026-06-22 testv2
2026-06-22 update node ver22
2026-06-22 deploy: bcb5259d39ec571dd337c59d90f50a5344b6ba1f
2026-06-22 deploy: abb5aea0f911b378ffaf37dafe3390e676b7fb31
2026-06-22 chuyển app sang giao diện web để deploy vercel demo
2026-06-22 Ép Git tải thư mục build/web lên Vercel
2026-06-22 thêm time và các icon cho giống điện thoại thật
2026-06-22 xóa time, pin, sóng, mạng, giữ bottom vuốt
2026-06-22 sửa link cho đẹp
2026-06-24 tạo database, thêm macc address, chuẩn bị fake data
2026-06-24 fake data thành công nhưng bug không load trang dashboard phải F5
2026-06-25 cảnh báo, lịch sử cảnh báo, trục X Y cho chart, piechart, kích hoạt relay, hẹn giờ bật relay
2026-06-25 lỗi vercel
2026-06-25 lỗi vercel piechart
2026-06-25 deploy: 9e6b78a3b290e6f5ce35e79284cd75851d46d557
2026-06-26 mobile bug, chỉnh lại icon hướng dẫn xử lý
2026-06-26 deploy: e9d5718f9017b7ac5c915ed0fedfef65272ab89f
2026-06-26 gộp cron job vô server.js để deploy 1 thể
2026-06-26 deploy web build
2026-06-26 fix: cấu hình CORS đầy đủ để fix lỗi preflight từ Web
2026-06-26 sửa lỗi render
2026-06-26 theo antigravity sửa lỗi crocs
2026-06-26 deploy: 1b5e3cdb752add27c80c29dc5db60ba019659b44
2026-06-26 thiếu parameter
2026-06-26 fix landing page, tạo nút về landing page trong dashboard
2026-06-26 cmt game
2026-06-26 deploy: dea537b755c0ca750e69e458b733b05daad127a8
2026-06-26 chỉnh dashboard
2026-06-26 deploy: e357b7c66393b31e248f1347f7f46ef45926c495
2026-06-26 sửa cái hoạt động 12H qua, có gì reroll
2026-06-26 deploy: 3a90c3794b343edba67003d603c156f55c27fd7c
2026-06-26 light mode, google fail
2026-06-26 deploy: 59a238886fda0b8438663560be65ae564a3a36db
2026-06-27 chỉnh biểu đồ aver 1 tiếng cho 3 cảm biến còn lại
2026-06-27 bug vercel
2026-06-27 bug vercel name
2026-06-27 deploy: 3655173abb058fb62365dff2af9e4881eb993426
